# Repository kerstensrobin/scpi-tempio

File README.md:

# Nacho.works SCPI-TempIO

> USB-connected environmental sensor and GPIO control module based on the STM32G0B1KBTx.

> [!WARNING]
> **Hardware v0.01 is not ready for production.** The board must be revised before another batch is ordered. Open issues:
>
> 1. **J1 VTref is on VBUS (5 V) on the PCB.** The schematic was corrected (VTref to 3V3), but the PCB was never updated from it. With 5 V on VTref, a programmer that sets its I/O level from VTref (such as a genuine ST-Link) may drive SWD at 5 V into a 3.3 V MCU. Existing boards need a bodge: cut J1 pin 1 from VBUS and wire it to 3V3.
> 2. **The schematic hotfix also moved C7** (1 µF, the AP2112K input capacitor) from VBUS to 3V3. It must go back on VBUS before the PCB is updated from the schematic, or the regulator loses its input capacitor.
> 3. **U1 symbol still named STM32G070KBTx** in the schematic's symbol cache; the fitted part is the STM32G0B1KBT6.
> 4. **Gerbers in `hardware/production/` are from v0.01** and contain issue 1. Regenerate them after the fixes.
>
> Before ordering: fix the above, update the PCB from the schematic, run DRC with schematic parity, and check that J1 pin 1 is on 3V3 and C7 on VBUS.

---

## Repository Contents

| Path          | Contents                                                        |
| ------------- | --------------------------------------------------------------- |
| `hardware/`   | KiCad project `SCPI_tempIO` (board with rounded tracks), `production/` holds the v0.01 JLC outputs |
| `firmware/`   | STM32CubeMX + CMake project, TinyUSB submodule in `firmware/lib/tinyusb` |
| `examples/`   | Host-side example scripts (`tempio_demo.py` runs every command) |

---

## Overview

This module is a small USB-connected development and test interface based on the STM32G0B1KBTx microcontroller.

It provides:

* USB serial SCPI interface
* Temperature measurement
* Humidity measurement
* 8 configurable GPIO pins
* I2C expansion connectors
* Breadboard-friendly operation
* SWD programming/debug interface

The module is intended for:

* breadboard prototyping
* embedded testing
* automation experiments
* SCPI/VISA software integration
* GPIO scripting from a PC

---

## Features

## Environmental sensing

Integrated sensor:

* SHT41 temperature + humidity sensor (I2C1, address 0x44)

Typical measurements:

| Parameter   | Typical Accuracy |
| ----------- | ---------------- |
| Temperature | ±0.2 °C          |
| Humidity    | ±1.8 %RH         |

---

## USB interface

The module connects to a host PC through USB-C and shows up as two interfaces at once. Both run the same SCPI commands and share one error queue:

| Interface          | Use it for                                                         |
| ------------------ | ------------------------------------------------------------------ |
| USBTMC (USB488)    | VISA / instrument software: `USB0::0x1209::0x0001::<serial>::INSTR` |
| CDC serial port    | Terminals, pyserial, anything without VISA; no driver needed       |

USB identification:

| Field        | Value                                   |
| ------------ | --------------------------------------- |
| VID:PID      | 1209:0001 (pid.codes test ID, dev only) |
| Manufacturer | Nacho.works                             |
| Product      | SCPI-TempIO v01                         |
| Serial       | 96-bit MCU unique ID, 24 hex characters |

The device appears as:

* COMx on Windows
* /dev/ttyACMx on Linux, also as `/dev/serial/by-id/usb-Nacho.works_SCPI-TempIO_v01_<serial>-if00`
* /dev/cu.usbmodem* on macOS

It is a native USB device, so the baud rate and other serial settings are ignored; any value works.

## VISA (USBTMC)

VISA resource string:

```text
USB0::0x1209::0x0001::<serial>::INSTR
```

The serial is the one returned by `*IDN?`. Some tools print the IDs in decimal: `USB0::4617::1::<serial>::0::INSTR` is the same instrument.

What USBTMC adds over the serial port:

* Found by VID/PID/serial, independent of COM port or ttyACM numbering
* Explicit message boundaries, no line-termination guessing
* Device clear (`viClear`): drops a half-sent command and any unread response
* Status byte (`viReadSTB`): bit 4 MAV = response waiting, bit 2 EAV = error queue not empty
* Indicator pulse ("identify" in NI MAX): the LED blinks fast for 2 s

Host setup:

* **Windows / macOS:** install NI-VISA or Keysight IO Libraries, they include the USBTMC driver.
* **Linux:** works with pyvisa + pyvisa-py (`pip install pyvisa pyvisa-py pyusb`). Install the udev rule once so a normal user can open the device and the kernel `usbtmc` driver does not claim it:

  ```sh
  sudo cp examples/99-scpi-tempio.rules /etc/udev/rules.d/
  sudo udevadm control --reload
  ```

  Then replug the unit. Without the rule, pyvisa lists the device but fails with `Resource busy`.

pyvisa-py (0.8) implements read/write/query on USB, but not `read_stb()` or `clear()`; those need NI-VISA or Keysight VISA. The firmware supports both.

The USBTMC interface is deliberately interface 0: pyvisa-py detaches the kernel driver from interface 0 when it opens a USB instrument, and would otherwise disconnect the serial port.

---

## GPIO Interface

The module exposes 8 configurable GPIO pins, DIO0–DIO7 (MCU pins PA0–PA7).

## GPIO capabilities

Each pin can be configured as:

* Digital input (default after power-up and `*RST`)
* Digital output (push-pull)
* Open-drain output
* PWM output (hardware timer, 0.1 Hz to 32 MHz)

## GPIO voltage levels

IMPORTANT:

```text
GPIO pins are 3.3V logic only.
```

Do not apply voltages above 3.3V.

## GPIO protection

Each GPIO pin includes a series protection resistor.

This improves tolerance against:

* accidental shorts
* output contention
* breadboard wiring mistakes

---

## Connector Pinout

## GPIO Header (J2)

2×5 box header, 2.54 mm pitch. Top view, pin 1 top-left:

```text
          ┌──────────────┐
  3V3   ■ 1            2 ●  DIO0
  DIO1  ● 3            4 ●  DIO2
  DIO3  ● 5            6 ●  DIO4
  DIO5  ● 7            8 ●  DIO6
  DIO7  ● 9           10 ●  GND
          └──────────────┘
```

Pin 1 (3V3) has the square pad on the bottom side and the triangle mark on the header housing. The pins alternate between the two rows: odd pins in one row, even pins in the other. DIO0 sits right next to 3V3, and GND is in the opposite corner.

| Pin | Function |
| --- | -------- |
| 1   | 3V3      |
| 2   | DIO0     |
| 3   | DIO1     |
| 4   | DIO2     |
| 5   | DIO3     |
| 6   | DIO4     |
| 7   | DIO5     |
| 8   | DIO6     |
| 9   | DIO7     |
| 10  | GND      |

## I2C Expansion (J4, J5)

Shared with the on-board SHT41 bus (pull-ups on board).

| Pin | Function |
| --- | -------- |
| 1   | 3V3      |
| 2   | SCL      |
| 3   | SDA      |
| 4   | GND      |

---

## SCPI Command Interface

## General

Commands are ASCII text terminated by `\n` or `\r\n`. Responses end with `\n`.

Headers are case-insensitive and accept both the short and the long form, for example `MEAS:TEMP?` and `measure:temperature?` are the same query.

Several commands can be sent on one line, separated by `;`. Each command must be written out in full (`MEAS:TEMP?;MEAS:HUM?`); the responses come back on one line, also separated by `;`.

Examples:

```text
*IDN?
MEAS:TEMP?
DIG:PIN0 1
```

---

## Supported Commands

| Command                       | Description                                  |
| ----------------------------- | -------------------------------------------- |
| `*IDN?`                       | Identification                               |
| `*RST`                        | Reset: all GPIO pins back to input           |
| `*CLS`                        | Clear the error queue                        |
| `*OPC?`                       | Always returns `1`                           |
| `*TST?`                       | Self test: `0` = SHT41 found, `1` = not found |
| `SYSTem:ERRor[:NEXT]?`        | Read and remove the oldest error             |
| `SYSTem:VERSion?`             | SCPI version, `1999.0`                       |
| `MEASure:TEMPerature?`        | Temperature in °C                            |
| `MEASure:HUMidity?`           | Relative humidity in %RH                     |
| `MEASure:ALL?`                | `temperature,humidity`                       |
| `DIGital:PIN<n>:MODE IN\|OUT\|OD` | Set pin mode                             |
| `DIGital:PIN<n>:MODE?`        | Read pin mode                                |
| `DIGital:PIN<n> 0\|1\|OFF\|ON` | Set output level                            |
| `DIGital:PIN<n>?`             | Read pin level                               |
| `DIGital:PIN<n>:PWM <freq>[,<duty>]` | Start PWM output                       |
| `DIGital:PIN<n>:PWM?`         | Actual frequency and duty                    |
| `DIGital:PORT?`               | Read all 8 pins                              |

`<n>` is 0–7.

---

## Identification

### Query device identification

```text
*IDN?
```

Example response:

```text
Nacho.works,SCPI-TempIO v01,2038393741565017002D005E,0.3
```

Format:

```text
MANUFACTURER,MODEL,SERIAL,FIRMWARE_VERSION
```

---

# Environmental Measurements

Every query starts a new high-precision measurement (~10 ms).

If the sensor does not respond, the value is returned as `9.91E37` (SCPI "not a number") and error `-240` is queued.

## Temperature measurement

```text
MEAS:TEMP?
```

Example response:

```text
23.41
```

Units:

```text
°C
```

---

## Humidity measurement

```text
MEAS:HUM?
```

Example response:

```text
45.72
```

Units:

```text
%RH
```

---

## Combined measurement

```text
MEAS:ALL?
```

Example response:

```text
23.41,45.72
```

Format:

```text
TEMPERATURE,HUMIDITY
```

Both values come from the same measurement.

---

# GPIO Commands

## Configure GPIO mode

### Input mode

```text
DIG:PIN0:MODE IN
```

### Output mode

```text
DIG:PIN0:MODE OUT
```

### Open-drain mode

```text
DIG:PIN0:MODE OD
```

### Read mode

```text
DIG:PIN0:MODE?
```

Example response:

```text
OUT
```

---

## Set GPIO output state

### Set HIGH

```text
DIG:PIN0 1
```

### Set LOW

```text
DIG:PIN0 0
```

The level is remembered while a pin is an input, and is applied when the pin is switched to OUT or OD. This lets you set the level first and then enable the output without a glitch.

---

## Read GPIO state

```text
DIG:PIN0?
```

Example response:

```text
1
```

This reads the actual pin level, in every mode.

---

## PWM output

Each DIO pin can output a hardware PWM signal, generated by a timer in the MCU. It is exact and jitter-free, and keeps running without further USB traffic.

```text
DIG:PIN0:PWM 1000          1 kHz, 50 % duty
DIG:PIN0:PWM 2.5MHZ,25     2.5 MHz, 25 % duty
DIG:PIN4:PWM 0.5,10%       0.5 Hz, 10 % duty
DIG:PIN0:PWM?              actual frequency,duty, e.g. 1000,50
DIG:PIN0:MODE OUT          stop PWM, back to normal output
```

* Frequency: 0.1 Hz to 32 MHz, as a plain number in Hz or with `HZ`, `KHZ` or `MHZ` (SCPI `MHZ` is megahertz).
* Duty: 0 to 100 %, default 50 %.
* `DIG:PIN<n>:MODE?` returns `PWM` while PWM is running. `DIG:PIN<n>:MODE IN|OUT|OD` or `*RST` stops it.
* The timer rounds to the nearest reachable setting; `DIG:PIN<n>:PWM?` returns what is actually generated. At high frequencies the duty resolution gets coarse: at 32 MHz only 0, 50 and 100 % are possible.
* Signal quality: the 330 Ω series resistor and the probe or cable capacitance round the edges. Expect a clean square wave up to roughly 5–10 MHz.

Pins that share a timer also share the frequency:

| Timer | Pins                  | Shared                                           |
| ----- | --------------------- | ------------------------------------------------ |
| TIM2  | DIO0, DIO1, DIO5      | Frequency; DIO0 and DIO5 also share the duty (same channel) |
| TIM15 | DIO2, DIO3            | Frequency                                        |
| TIM14 | DIO4                  | —                                                |
| TIM16 | DIO6                  | —                                                |
| TIM17 | DIO7                  | —                                                |

Setting a different frequency on a pin whose timer is already in use gives error `-221`; stop the other pin first or use the same frequency.

---

## Read all GPIO states

```text
DIG:PORT?
```

Example response:

```text
10100110
```

The first character is DIO7 and the last is DIO0. In the example above, DIO1, DIO2, DIO5 and DIO7 are high.

---

## Errors

Errors are queued (up to 8) and read one at a time with `SYST:ERR?`. `0,"No error"` means the queue is empty.

| Code | Meaning                                               |
| ---- | ----------------------------------------------------- |
| -108 | Parameter not allowed                                 |
| -109 | Missing parameter                                     |
| -113 | Undefined header (unknown command)                    |
| -114 | Header suffix out of range (pin number not 0–7)       |
| -120 | Numeric data error (number expected)                  |
| -131 | Invalid suffix (unit other than HZ, KHZ, MHZ)         |
| -221 | Settings conflict (PWM timer shared with another pin) |
| -222 | Data out of range (PWM frequency or duty)             |
| -223 | Too much data (response line too long)                |
| -224 | Illegal parameter value                               |
| -240 | Hardware error (SHT41 not responding)                 |
| -350 | Queue overflow                                        |
| -363 | Input buffer overrun (command line over 127 characters) |

---

## Status LED

| LED               | Meaning                                  |
| ----------------- | ---------------------------------------- |
| Blinking (2 Hz)   | Not enumerated by a USB host             |
| On                | Enumerated, ready                        |
| Short off-flick   | A command was received                   |
| Fast blink (2 s)  | Identify request (USBTMC indicator pulse) |

---

## Programming and Debugging

## SWD Interface (J1)

The module includes a 10-pin 1.27 mm Cortex debug connector.

Signals:

| Signal | Description    |
| ------ | -------------- |
| SWDIO  | Debug data     |
| SWCLK  | Debug clock    |
| NRST   | Reset          |
| VTref  | Target voltage |
| GND    | Ground         |

Compatible programmers:

* ST-Link V2
* ST-Link V3

Notes:

* The SWD cable does not power the board. Power it from USB.
* With a Treedix JTAG/SWD adapter board, install the VCC→VREF jumper. Otherwise the ST-Link reads about 1.7 V (floating VTref) and will not connect.
* On v0.01 boards, VTref (J1 pin 1) is routed to VBUS (5 V) instead of 3V3; see the warning at the top. Unless the board has been bodged, the ST-Link reports about 5 V target voltage and may drive SWD at that level. Bodge J1 pin 1 to 3V3 before connecting a programmer, or flash a blank board over USB DFU instead.
* Put the scope or multimeter ground on J2 pin 10 (GND), never on pin 1 (3V3). A bench scope's ground is mains earth, which the PC's USB ground is also tied to, so clipping it onto 3V3 shorts the regulator output. On one v0.01 board this destroyed U2 (AP2112K), leaving the MCU running on 5 V.

---

## Firmware Development

Toolchain:

* STM32CubeMX for pin and clock configuration (`firmware/tempio.ioc`, toolchain set to CMake)
* CMake + arm-none-eabi-gcc (the one bundled with STM32CubeIDE works)
* STM32 HAL
* TinyUSB 0.21.0 (git submodule in `firmware/lib/tinyusb`)
* STM32CubeProgrammer CLI or any SWD tool for flashing

Source layout:

| Path                             | Contents                                   |
| -------------------------------- | ------------------------------------------ |
| `firmware/App/`                  | Application code (SCPI, SHT41, DIO, USB CDC + USBTMC) |
| `firmware/App/Inc/version.h`     | Manufacturer, model and firmware version   |
| `firmware/Src`, `firmware/Inc`   | CubeMX generated code                      |

Application code lives in `App/` and is called from `main.c` inside the `USER CODE` sections, so regenerating from CubeMX keeps it.

USB is deliberately left disabled in CubeMX. TinyUSB drives the peripheral, and `App/Src/usb_hw.c` sets up the USB clock (HSI48 trimmed by the CRS, no crystal needed) and the interrupt handler.

## Build

```sh
git submodule update --init
cd firmware
cmake -S . -B build/Debug -G "Unix Makefiles" \
      -DCMAKE_TOOLCHAIN_FILE=cmake/gcc-arm-none-eabi.cmake -DCMAKE_BUILD_TYPE=Debug
cmake --build build/Debug
```

`arm-none-eabi-gcc` must be on the `PATH`. With Ninja installed, `cmake --preset Debug` also works.

## Flash

```sh
STM32_Programmer_CLI -c port=SWD mode=UR -w build/Debug/tempio.elf -v -rst
```

---

## Electrical Specifications

| Parameter          | Value         |
| ------------------ | ------------- |
| USB input voltage  | 5V            |
| Logic voltage      | 3.3V          |
| GPIO voltage range | 0–3.3V        |
| GPIO direction     | Configurable  |
| MCU                | STM32G0B1KBTx |
| Sensor             | SHT41         |

---

## Safety Notes

## IMPORTANT

Do not:

* connect GPIO pins directly to mains voltage
* exceed 3.3V on GPIO pins
* drive motors directly from GPIO pins
* short outputs together intentionally

For inductive loads:

* use transistors or MOSFETs
* use flyback diodes

---

## Example Python Usage

`examples/tempio_demo.py` connects to the unit and runs every command once:

```sh
pip install pyserial
python3 examples/tempio_demo.py            # auto-detect on Linux/macOS
python3 examples/tempio_demo.py COM5       # or give the port
```

Minimal VISA version:

```python
import pyvisa

rm = pyvisa.ResourceManager()          # '@py' for pyvisa-py
print(rm.list_resources())

inst = rm.open_resource('USB0::0x1209::0x0001::2038393741565017002D005E::INSTR')
print(inst.query('*IDN?'))
print(inst.query('MEAS:ALL?'))
inst.write('DIG:PIN0:MODE OUT')
inst.write('DIG:PIN0 1')
```

Minimal serial version:

```python
import serial

s = serial.Serial('/dev/ttyACM0', timeout=1)

s.write(b'*IDN?\n')
print(s.readline().decode())

s.write(b'MEAS:TEMP?\n')
print(s.readline().decode())

s.write(b'DIG:PIN0:MODE OUT\n')
s.write(b'DIG:PIN0 1\n')
```

---

## Revision

| Revision | Description                                          |
| -------- | ---------------------------------------------------- |
| 1.0      | Initial draft                                        |
| 1.1      | Firmware 0.1: USB CDC SCPI, SHT41, GPIO; MCU corrected to STM32G0B1 |
| 1.2      | Firmware 0.2: added USBTMC/USB488 interface (VISA) next to CDC |
| 1.3      | Firmware 0.3: PWM output on all DIO pins; hardware v0.01 production warning |

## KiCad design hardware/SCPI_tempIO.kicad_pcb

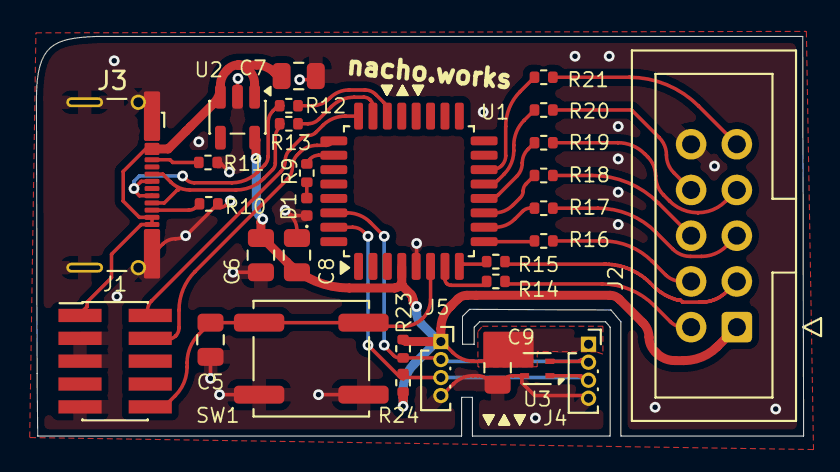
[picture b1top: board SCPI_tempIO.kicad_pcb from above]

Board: 2 copper layers, 42.6 x 22.2 mm, 30 parts (0 on the bottom side), 32 nets.

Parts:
C5, C6, C9: 100n; C_0805_2012Metric
C7: 1u; C_0805_2012Metric
C8: 4.7n; C_0805_2012Metric
D1: LED; LED_0402_1005Metric
J1: Conn_ARM_JTAG_SWD_10; PinHeader_2x05_P1.27mm_Vertical_SMD
J2: Conn_02x05_Counter_Clockwise; IDC-Header_2x05_P2.54mm_Vertical
J3: USB_C_Receptacle_USB2.0_16P; USB_C_Receptacle_G-Switch_GT-USB-7025
J4, J5: Conn_01x04_Pin; PinSocket_1x04_P1.00mm_Vertical
R9: 1000; R_0402_1005Metric
R10, R11: 5.1k; R_0402_1005Metric
R12, R13: 22; R_0402_1005Metric
R14, R15, R16, R17, R18, R19, R20, R21: 330; R_0402_1005Metric
R23, R24: 10k; R_0402_1005Metric
SW1: SW_SPST; SW_Push_1P1T_NO_CK_KSC7xxJ
U1: STM32G070KBTx; LQFP-32_7x7mm_P0.8mm
U2: AP2112K-3.3; SOT-23-5
U3: SHT4x; Sensirion_DFN-4_1.5x1.5mm_P0.8mm_SHT4x_NoCentralPad

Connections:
/3v3: C6.1, C8.1, C9.1, J2.1, J4.1, J5.1, R23.1, R24.1, U1.4 (VDD), U2.5 (VOUT), U3.3 (VDD)
/SHT4x_sub/SCL: J4.2, J5.2, R23.2, U1.30 (PB6), U3.2 (SCL)
/SHT4x_sub/SDA: J4.3, J5.3, R24.2, U1.31 (PB7), U3.1 (SDA)
/USBD+: R13.2, U1.23 (PA10/PA12)
/USBD-: R12.2, U1.22 (PA9/PA11)
GND: C5.2, C6.2, C7.2, C8.2, C9.2, D1.1 (K), J1.3 (GND), J1.5 (GND), J1.9 (GNDDetect), J2.10, J3.A1 (GND), J3.A12 (GND), J3.B1 (GND), J3.B12 (GND), J3.SH (SHIELD), J4.4, J5.4, R10.2, R11.2, SW1.2 (B), U1.5 (VSS), U2.2 (GND), U3.4 (VSS)
unnamed: D1.2 (A), R9.2
unnamed: J1.4 (SWCLK/TCK), U1.25 (PA14)
unnamed: J1.2 (SWDIO/TMS), U1.24 (PA13)
unnamed: C7.1, J1.1 (VTref), J3.A4 (VBUS), J3.A9 (VBUS), J3.B4 (VBUS), J3.B9 (VBUS), U2.1 (VIN), U2.3 (EN)
unnamed: C5.1, J1.10 (~RESET), SW1.1 (A), U1.6 (NRST)
unnamed: J2.2, R14.2
unnamed: J2.3, R15.2
unnamed: J2.4, R16.2
unnamed: J2.5, R17.2
unnamed: J2.6, R18.2
unnamed: J2.7, R19.2
unnamed: J2.8, R20.2
unnamed: J2.9, R21.2
unnamed: J3.A5 (CC1), R11.1
unnamed: J3.B5 (CC2), R10.1
unnamed: J3.A6 (D+), J3.B6 (D+), R13.1
unnamed: J3.A7 (D-), J3.B7 (D-), R12.1
unnamed: R14.1, U1.7 (PA0)
unnamed: R15.1, U1.8 (PA1)
unnamed: R16.1, U1.9 (PA2)
unnamed: R17.1, U1.10 (PA3)
unnamed: R18.1, U1.11 (PA4)
unnamed: R19.1, U1.12 (PA5)
unnamed: R20.1, U1.13 (PA6)
unnamed: R21.1, U1.14 (PA7)
unnamed: R9.1, U1.26 (PA15)

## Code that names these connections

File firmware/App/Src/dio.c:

#include "main.h"
#include "dio.h"

#define DIO_PORT GPIOA

/* Timer channel per DIO pin, from the STM32G0B1 alternate function table.
 * PA5 only has TIM2_CH1, the same channel as PA0. */
typedef struct {
  TIM_TypeDef *tim;
  uint8_t ch;
  uint8_t af;
} pwm_map_t;

static const pwm_map_t pwm_map[DIO_COUNT] = {
  {TIM2,  1, GPIO_AF2_TIM2},  /* DIO0 PA0 */
  {TIM2,  2, GPIO_AF2_TIM2},  /* DIO1 PA1 */
  {TIM15, 1, GPIO_AF5_TIM15}, /* DIO2 PA2 */
  {TIM15, 2, GPIO_AF5_TIM15}, /* DIO3 PA3 */
  {TIM14, 1, GPIO_AF4_TIM14}, /* DIO4 PA4 */
  {TIM2,  1, GPIO_AF2_TIM2},  /* DIO5 PA5 */
  {TIM16, 1, GPIO_AF5_TIM16}, /* DIO6 PA6 */
  {TIM17, 1, GPIO_AF5_TIM17}, /* DIO7 PA7 */
};

static dio_mode_t modes[DIO_COUNT];

/* ---------- timer helpers ---------- */

static uint32_t timer_clock(void)
{
  uint32_t pclk = HAL_RCC_GetPCLK1Freq();
  return (RCC->CFGR & RCC_CFGR_PPRE_2) ? 2 * pclk : pclk; /* x2 when APB is divided */
}

static void timer_clk_enable(TIM_TypeDef *t)
{
  if (t == TIM2) __HAL_RCC_TIM2_CLK_ENABLE();
  else if (t == TIM14) __HAL_RCC_TIM14_CLK_ENABLE();
  else if (t == TIM15) __HAL_RCC_TIM15_CLK_ENABLE();
  else if (t == TIM16) __HAL_RCC_TIM16_CLK_ENABLE();
  else if (t == TIM17) __HAL_RCC_TIM17_CLK_ENABLE();
}

static volatile uint32_t *ccr_reg(TIM_TypeDef *t, unsigned ch)
{
  return &t->CCR1 + (ch - 1);
}

/* Another pin (not `pin`) running PWM on the same timer, and optionally the same channel. */
static int other_pwm_user(unsigned pin, bool same_channel)
{
  for (unsigned j = 0; j < DIO_COUNT; j++) {
    if (j == pin || modes[j] != DIO_MODE_PWM || pwm_map[j].tim != pwm_map[pin].tim) continue;
    if (!same_channel || pwm_map[j].ch == pwm_map[pin].ch) return (int)j;
  }
  return -1;
}

static void channel_start(TIM_TypeDef *t, unsigned ch, uint32_t ccr)
{
  volatile uint32_t *ccmr = ch <= 2 ? &t->CCMR1 : &t->CCMR2;
  unsigned sh = ((ch - 1) & 1) * 8;
  uint32_t clear = (0x3u << sh) | (0x7u << (4 + sh)) | (1u << (16 + sh)); /* CCxS, OCxM */
  *ccmr = (*ccmr & ~clear) | (6u << (4 + sh)) | (1u << (3 + sh));         /* PWM mode 1, preload */
  *ccr_reg(t, ch) = ccr;
  t->CCER |= 1u << ((ch - 1) * 4);
}

static void channel_stop(TIM_TypeDef *t, unsigned ch)
{
  t->CCER &= ~(1u << ((ch - 1) * 4));
}

static void pwm_release(unsigned pin)
{
  const pwm_map_t *m = &pwm_map[pin];
  modes[pin] = DIO_MODE_IN; /* so other_pwm_user() no longer counts this pin */
  if (other_pwm_user(pin, true) < 0) channel_stop(m->tim, m->ch);
  if (other_pwm_user(pin, false) < 0) m->tim->CR1 &= ~TIM_CR1_CEN;
}

/* ---------- public API ---------- */

void dio_init(void)
{
  __HAL_RCC_GPIOA_CLK_ENABLE();
  for (unsigned i = 0; i < DIO_COUNT; i++) {
    HAL_GPIO_WritePin(DIO_PORT, 1u << i, GPIO_PIN_RESET);
    dio_set_mode(i, DIO_MODE_IN);
  }
}

void dio_set_mode(unsigned pin, dio_mode_t mode)
{
  if (modes[pin] == DIO_MODE_PWM) pwm_release(pin);

  GPIO_InitTypeDef init = {0};
  init.Pin = 1u << pin;
  init.Pull = GPIO_NOPULL;
  init.Speed = GPIO_SPEED_FREQ_LOW;
  switch (mode) {
    case DIO_MODE_OUT: init.Mode = GPIO_MODE_OUTPUT_PP; break;
    case DIO_MODE_OD:  init.Mode = GPIO_MODE_OUTPUT_OD; break;
    default:           init.Mode = GPIO_MODE_INPUT; mode = DIO_MODE_IN; break;
  }
  /* ODR keeps its value across mode changes, so outputs come up at the last written level. */
  HAL_GPIO_Init(DIO_PORT, &init);
  modes[pin] = mode;
}

dio_mode_t dio_get_mode(unsigned pin)
{
  return modes[pin];
}

void dio_write(unsigned pin, bool level)
{
  HAL_GPIO_WritePin(DIO_PORT, 1u << pin, level ? GPIO_PIN_SET : GPIO_PIN_RESET);
}

bool dio_read(unsigned pin)
{
  return HAL_GPIO_ReadPin(DIO_PORT, 1u << pin) == GPIO_PIN_SET;
}

uint8_t dio_read_port(void)
{
  return (uint8_t)(DIO_PORT->IDR & 0xFF);
}

dio_err_t dio_set_pwm(unsigned pin, uint64_t freq_mhz, uint32_t duty_c100)
{
  if (freq_mhz < DIO_PWM_MIN_MHZ || freq_mhz > DIO_PWM_MAX_MHZ) return DIO_ERR_RANGE;
  if (duty_c100 > DIO_PWM_DUTY_MAX) return DIO_ERR_RANGE;

  const pwm_map_t *m = &pwm_map[pin];
  TIM_TypeDef *t = m->tim;

  /* Timer counts per period, split into prescaler and auto-reload so ARR is as large as
   * possible (best duty resolution). Integer math: frequency is in millihertz. */
  uint64_t clk_mhz = (uint64_t)timer_clock() * 1000u;
  uint64_t ticks = (clk_mhz + freq_mhz / 2) / freq_mhz;
  uint64_t span = (t == TIM2) ? (1ull << 32) : (1ull << 16); /* TIM2 is 32-bit, the rest 16-bit */
  uint32_t psc = ticks > span ? (uint32_t)((ticks - 1) / span) : 0; /* ceil(ticks / span) - 1 */
  uint32_t period = (uint32_t)((ticks + (psc + 1) / 2) / (psc + 1));
  if (period < 2) period = 2;
  uint32_t arr = period - 1;
  uint32_t ccr = (uint32_t)(((uint64_t)duty_c100 * period + DIO_PWM_DUTY_MAX / 2) / DIO_PWM_DUTY_MAX);

  /* Pins sharing the timer must agree on the period; DIO0/DIO5 also on the duty. */
  if (other_pwm_user(pin, false) >= 0 && (t->PSC != psc || t->ARR != arr)) return DIO_ERR_CONFLICT;
  if (other_pwm_user(pin, true) >= 0 && *ccr_reg(t, m->ch) != ccr) return DIO_ERR_CONFLICT;

  if (other_pwm_user(pin, false) < 0) {
    /* This pin is the timer's only user: (re)program the time base. The update event comes
     * after channel_start() so the preloaded duty applies from the first period on. */
    timer_clk_enable(t);
    t->CR1 = 0;
    t->PSC = psc;
    t->ARR = arr;
    t->CR1 = TIM_CR1_ARPE;
    channel_start(t, m->ch, ccr);
    t->EGR = TIM_EGR_UG; /* load PSC, ARR and CCR now */
    if (IS_TIM_BREAK_INSTANCE(t)) t->BDTR |= TIM_BDTR_MOE;
  } else {
    /* Timer already running for another pin: the new duty takes effect at the next period. */
    channel_start(t, m->ch, ccr);
  }
  t->CR1 |= TIM_CR1_CEN;

  GPIO_InitTypeDef init = {0};
  init.Pin = 1u << pin;
  init.Mode = GPIO_MODE_AF_PP;
  init.Pull = GPIO_NOPULL;
  init.Speed = GPIO_SPEED_FREQ_VERY_HIGH;
  init.Alternate = m->af;
  HAL_GPIO_Init(DIO_PORT, &init);
  modes[pin] = DIO_MODE_PWM;
  return DIO_OK;
}

void dio_get_pwm(unsigned pin, uint64_t *freq_mhz, uint32_t *duty_c100)
{
  if (modes[pin] != DIO_MODE_PWM) {
    *freq_mhz = 0;
    *duty_c100 = 0;
    return;
  }
  const pwm_map_t *m = &pwm_map[pin];
  uint64_t period = (uint64_t)m->tim->ARR + 1u;
  uint64_t div = ((uint64_t)m->tim->PSC + 1u) * period;
  *freq_mhz = ((uint64_t)timer_clock() * 1000u + div / 2) / div;
  *duty_c100 = (uint32_t)(((uint64_t)*ccr_reg(m->tim, m->ch) * DIO_PWM_DUTY_MAX + period / 2) / period);
}

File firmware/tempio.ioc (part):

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Mcu.Name=STM32G0B1K(B-C-E)Tx
Mcu.Package=LQFP32
Mcu.UserName=STM32G0B1KBTx
PA13.Mode=Serial_Wire
PA13.Signal=SYS_SWDIO
PA14-BOOT0.Mode=Serial_Wire
PA14-BOOT0.Signal=SYS_SWCLK
PA15.GPIOParameters=GPIO_Label
PA15.GPIO_Label=LED
PA15.Signal=GPIO_Output
PB6.Mode=I2C
PB6.Signal=I2C1_SCL
PB7.Mode=I2C
PB7.Signal=I2C1_SDA
RCC.HSE_VALUE=8000000
RCC.SYSCLKFreq_VALUE=64000000
RCC.SYSCLKSource=RCC_SYSCLKSOURCE_PLLCLK
board=custom

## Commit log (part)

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2026-05-26 intial dump
2026-05-26 added a hopefull README
2026-05-26 USB for contemporary goodness
2026-05-26 assigned gpio r footprints
2026-05-26 PCB BABY
2026-05-26 more fancy
2026-05-29 pullups and cap for the SHT4x
2026-05-30 sent to JLC noodleUSBp16
